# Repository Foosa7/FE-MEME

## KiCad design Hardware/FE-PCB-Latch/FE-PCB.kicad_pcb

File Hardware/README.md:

# Hardware
Includes Latch and Main PCB.

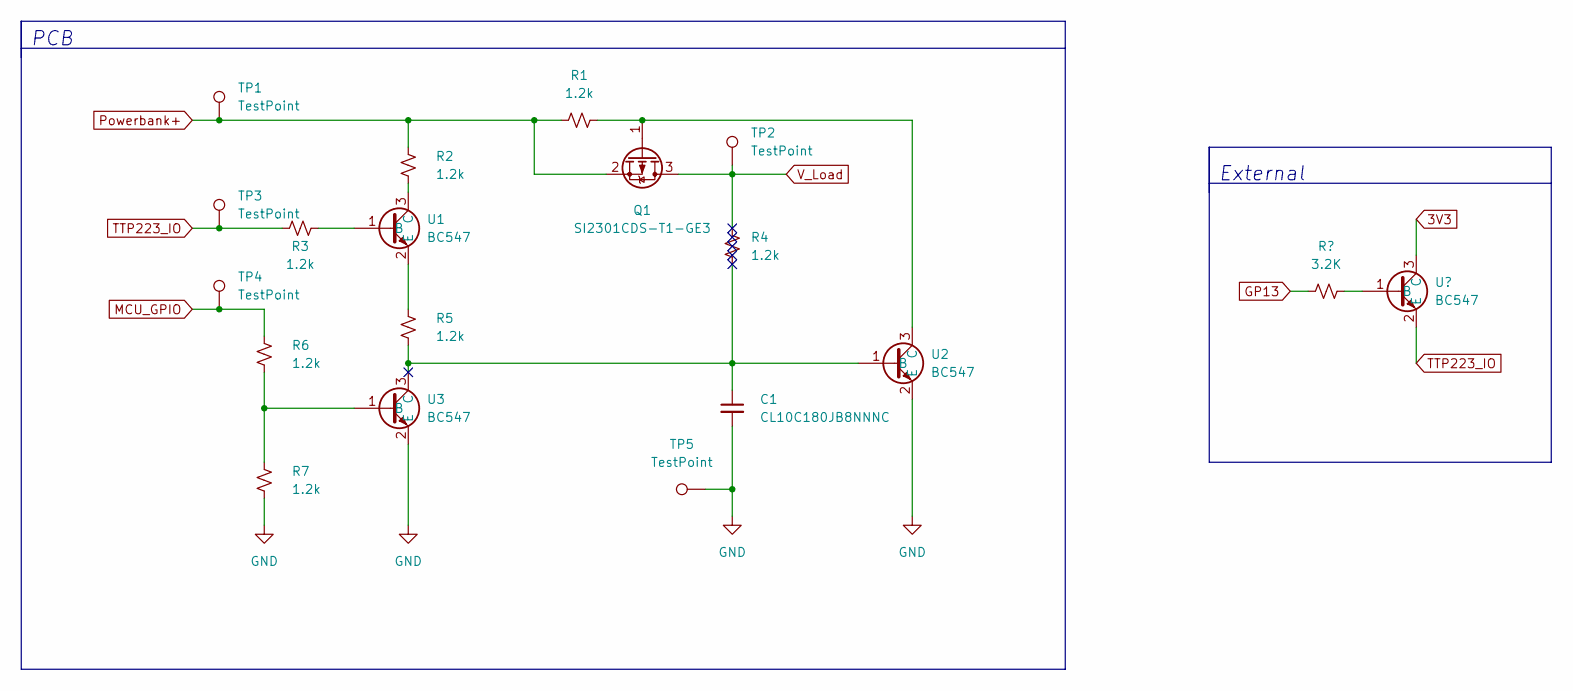
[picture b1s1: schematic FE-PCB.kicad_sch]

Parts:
C1: CL10C180JB8NNNC; C_0603_1608Metric; LCSC C1647
Q1: SI2301CDS-T1-GE3; SOT-23; LCSC C10487
R1, R2, R3, R4, R5, R6, R7: 1.2k; R_0603_1608Metric; LCSC C22765
TP1, TP2, TP3, TP4, TP5: TestPoint; cast_pad
U1, U2, U3: BC547; SOT-23; LCSC C105432

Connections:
GND: C1.2, R7.2, TP5.1, U2.2 (E), U3.2 (E)
MCU_GPIO: R6.1, TP4.1
unnamed: C1.1, R4.1, R5.2, U2.1 (B), U3.3 (C)
unnamed: Q1.1 (G), R1.2, U2.3 (C)
unnamed: R2.2, U1.3 (C)
unnamed: R3.2, U1.1 (B)
unnamed: R5.1, U1.2 (E)
unnamed: R6.2, R7.1, U3.1 (B)
Powerbank+: Q1.2 (S), R1.1, R2.1, TP1.1
TTP223_IO: R3.1, TP3.1
V_Load: Q1.3 (D), R4.2, TP2.1

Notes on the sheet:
External
PCB

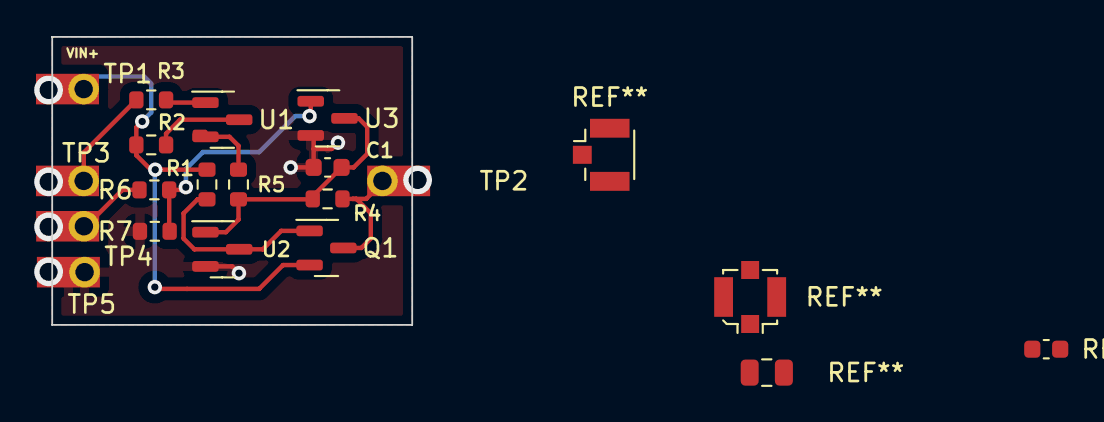
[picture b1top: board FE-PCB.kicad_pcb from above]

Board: 2 copper layers, 20.0 x 16.0 mm, 17 parts (0 on the bottom side), 11 nets.

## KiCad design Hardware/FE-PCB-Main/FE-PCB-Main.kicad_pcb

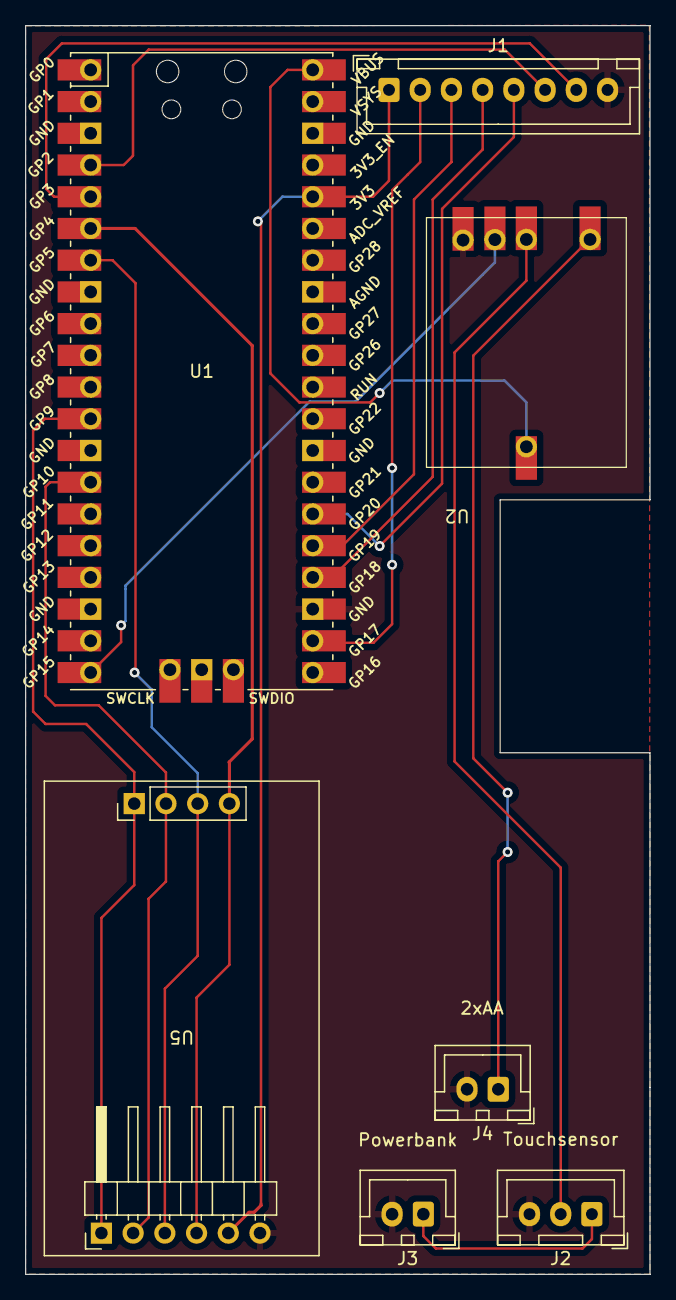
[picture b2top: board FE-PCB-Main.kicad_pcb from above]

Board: 2 copper layers, 50.0 x 100.0 mm, 7 parts (0 on the bottom side), 17 nets.

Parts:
J1: 8P-JST-XH; JST_XH_B8B-XH-A_1x08_P2.50mm_Vertical
J2: 3P-JST-XH; JST_XH_B3B-XH-A_1x03_P2.50mm_Vertical
J3, J4: 2P-JST-XH; JST_XH_B2B-XH-A_1x02_P2.50mm_Vertical
U1: Pico; RPi_Pico_SMD_TH
U2: Latch
U5: DS3231_PCB

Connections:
32K: U1.12 (GPIO9), U5.1 (32K)
+3V0: J2.1, J3.1
+3V3: J1.1, U1.36 (3V3), U5.5 (VCC)
+5V: J4.1, U2.1 (+VBus)
+LOAD: U1.40 (VBUS), U2.5 (+LOAD)
GND: J1.8, J2.3, J3.2, J4.2, U1.23 (GND), U2.4 (GND), U5.6 (GND)
I2C1_SCL: U1.7 (GPIO5), U5.3 (SCL)
I2C1_SDA: U1.6 (GPIO4), U5.4 (SDA)
SHUTDOWN: U1.20 (GPIO15), U2.3 (SHUTDOWN)
SQW: U1.14 (GPIO10), U5.2 (SQW)
TFT_BL: J1.2, U1.22 (GPIO17)
TFT_CS: J1.5, U1.26 (GPIO20)
TFT_DC: J1.4, U1.24 (GPIO18)
TFT_MOSI: J1.7, U1.5 (GPIO3)
TFT_RST: J1.3, U1.25 (GPIO19)
TFT_SCLK: J1.6, U1.4 (GPIO2)
TRIGGER: J2.2, U2.2 (TRIGGER)

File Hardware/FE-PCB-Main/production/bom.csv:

Designator,Footprint,Quantity,Value,LCSC Part #
J1,JST_XH_B8B-XH-A_1x08_P2.50mm_Vertical,1,8P-JST-XH ,
J2,JST_XH_B3B-XH-A_1x03_P2.50mm_Vertical,1,3P-JST-XH,
"J3, J4",JST_XH_B2B-XH-A_1x02_P2.50mm_Vertical,2,2P-JST-XH,
U1,RPi_Pico_SMD_TH,1,Pico,
U2,Latch,1,Latch,
U5,DS3231_PCB,1,DS3231_PCB,

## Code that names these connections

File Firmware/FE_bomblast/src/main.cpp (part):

/*

#define TFT_MISO 0 // RX PIN - Not Connected in display
#define TFT_SCLK 2 // In display, connect to SCL
#define TFT_MOSI 3 // In display, connect to SDA
#define TFT_CS   20  // In display, connect to CS
#define TFT_DC   18  // In display, connect to DC
#define TFT_RST  19  // In display, connect to RES
#define TFT_BL   17            // In display, connect to BLK
#define TFT_BACKLIGHT_ON HIGH  // Level to turn ON back-light (HIGH or LOW)

// #define PIN_WIRE_SDA (4u)
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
